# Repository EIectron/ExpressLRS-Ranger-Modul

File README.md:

<div align="center">
  <b>
   <h1>
      ExpressLRS Ranger
   </h1>
   <h6>
     V1
   </h6>
  </b>

</div>

## Features:
* E28 LoRa Modul
* ESP32 D4 Modul
* W2812B RGB Led
* I2C Screen Support

[Video](https://youtube.com/shorts/PznK_D05IgE)

### Build

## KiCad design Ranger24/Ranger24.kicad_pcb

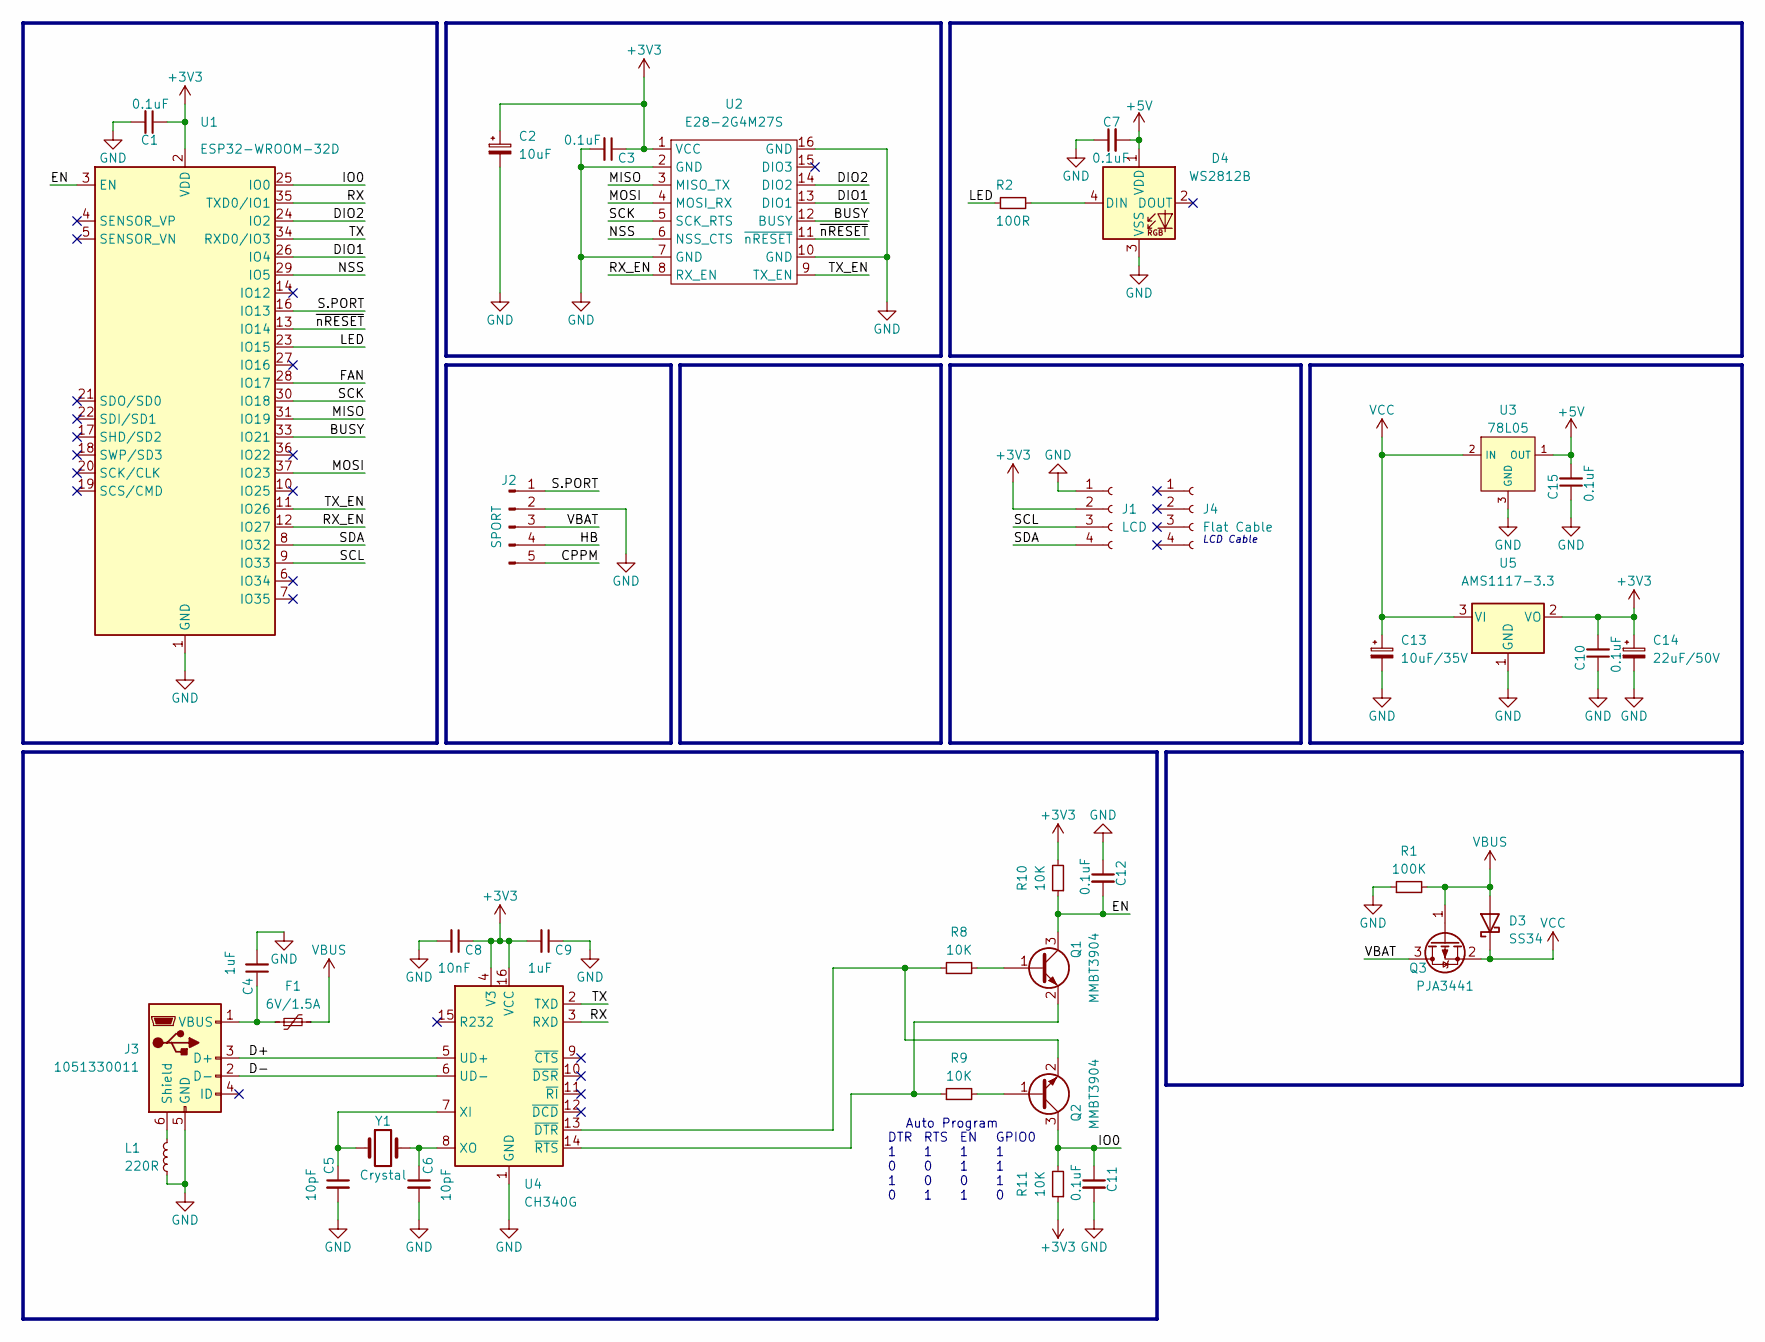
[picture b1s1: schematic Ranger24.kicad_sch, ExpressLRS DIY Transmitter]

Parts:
C1, C3, C7, C10, C11, C12, C15: 0.1uF; C_0603_1608Metric
C2: 10uF; CP_Elec_4x5.4
C4, C9: 1uF; C_0603_1608Metric
C5, C6: 10pF; C_0603_1608Metric
C8: 10nF; C_0603_1608Metric
C13: 10uF/35V; CP_Elec_5x5.3
C14: 22uF/50V; CP_Elec_6.3x5.7
D3: SS34; D_SMA
D4: WS2812B; LED_WS2812B_PLCC4_5.0x5.0mm_P3.2mm
F1: 6V/1.5A; Fuse_0805_2012Metric
J1: LCD; DS1020-05-04BT1
J2: SPORT; DS1023-10-1X5B81XTX
J3: 1051330011; USB_Micro-B_Molex-105133-0031
J4: Flat Cable
L1: 220R; L_0603_1608Metric
Q1, Q2: MMBT3904; SOT-23
Q3: PJA3441; SOT-23
R1: 100K; R_0603_1608Metric
R2: 100R; R_0603_1608Metric
R8, R9, R10, R11: 10K; R_0603_1608Metric
U1: ESP32-WROOM-32D; ESP32-WROOM-32
U2: E28-2G4M27S
U3: 78L05; SOT-23
U4: CH340G; SOIC-16_3.9x9.9mm_P1.27mm
U5: AMS1117-3.3; SOT-223-3_TabPin2
Y1: Crystal; Crystal_SMD_HC49-SD

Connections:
+3V3: C1.1, C2.1, C3.1, C8.1, C9.2, C10.2, C14.1, J1.2, R10.2, R11.1, U1.2 (VDD), U2.1 (VCC), U4.4 (V3), U4.16 (VCC), U5.2 (VO)
+5V: C7.2, C15.2, D4.1 (VDD), U3.1 (OUT)
/BUSY: U1.33 (IO21), U2.12 (BUSY)
/CPPM: J2.5
/D+: J3.3 (D+), U4.5 (UD+)
/D-: J3.2 (D-), U4.6 (UD-)
/DIO1: U1.26 (IO4), U2.13 (DIO1)
/DIO2: U1.24 (IO2), U2.14 (DIO2)
/EN: C12.2, Q1.3 (C), R10.1, U1.3 (EN)
/FAN: U1.28 (IO17)
/HB: J2.4
/IO0: C11.1, Q2.3 (C), R11.2, U1.25 (IO0)
/LED: R2.1, U1.23 (IO15)
/MISO: U1.31 (IO19), U2.3 (MISO_TX)
/MOSI: U1.37 (IO23), U2.4 (MOSI_RX)
/NSS: U1.29 (IO5), U2.6 (NSS_CTS)
/RX: U1.35 (TXD0/IO1), U4.3 (RXD)
/RX_EN: U1.12 (IO27), U2.8 (RX_EN)
/S.PORT: J2.1, U1.16 (IO13)
/SCK: U1.30 (IO18), U2.5 (SCK_RTS)
/SCL: J1.3, U1.9 (IO33)
/SDA: J1.4, U1.8 (IO32)
/TX: U1.34 (RXD0/IO3), U4.2 (TXD)
/TX_EN: U1.11 (IO26), U2.9 (TX_EN)
/VBAT: J2.3, Q3.3 (D)
/~nRESET: U1.13 (IO14), U2.11 (~nRESET)
GND: C1.2, C2.2, C3.2, C4.2, C5.2, C6.2, C7.1, C8.2, C9.1, C10.1, C11.2, C12.1, C13.2, C14.2, C15.1, D4.3 (VSS), J1.1, J2.2, J3.5 (GND), L1.1, R1.1, U1.1 (GND), U1.15 (GND), U1.38 (GND), U1.39 (GND), U2.2 (GND), U2.7 (GND), U2.10 (GND), U2.16 (GND), U3.3 (GND), U4.1 (GND), U5.1 (GND)
unnamed: D4.4 (DIN), R2.2
unnamed: J3.6 (Shield), L1.2
unnamed: C4.1, F1.1, J3.1 (VBUS)
unnamed: Q1.1 (B), R8.2
unnamed: Q1.2 (E), R9.1, U4.14 (~RTS)
unnamed: Q2.1 (B), R9.2
unnamed: Q2.2 (E), R8.1, U4.13 (~DTR)
unnamed: C5.1, U4.7 (XI), Y1.1
unnamed: C6.1, U4.8 (XO), Y1.2
VBUS: D3.2 (A), F1.2, Q3.1 (G), R1.2
VCC: C13.1, D3.1 (K), Q3.2 (S), U3.2 (IN), U5.3 (VI)

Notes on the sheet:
EN 1 1 0 1
DTR 1 0 1 0
Auto Program
GPIO0 1 1 1 0
RTS 1 0 0 1
LCD Cable

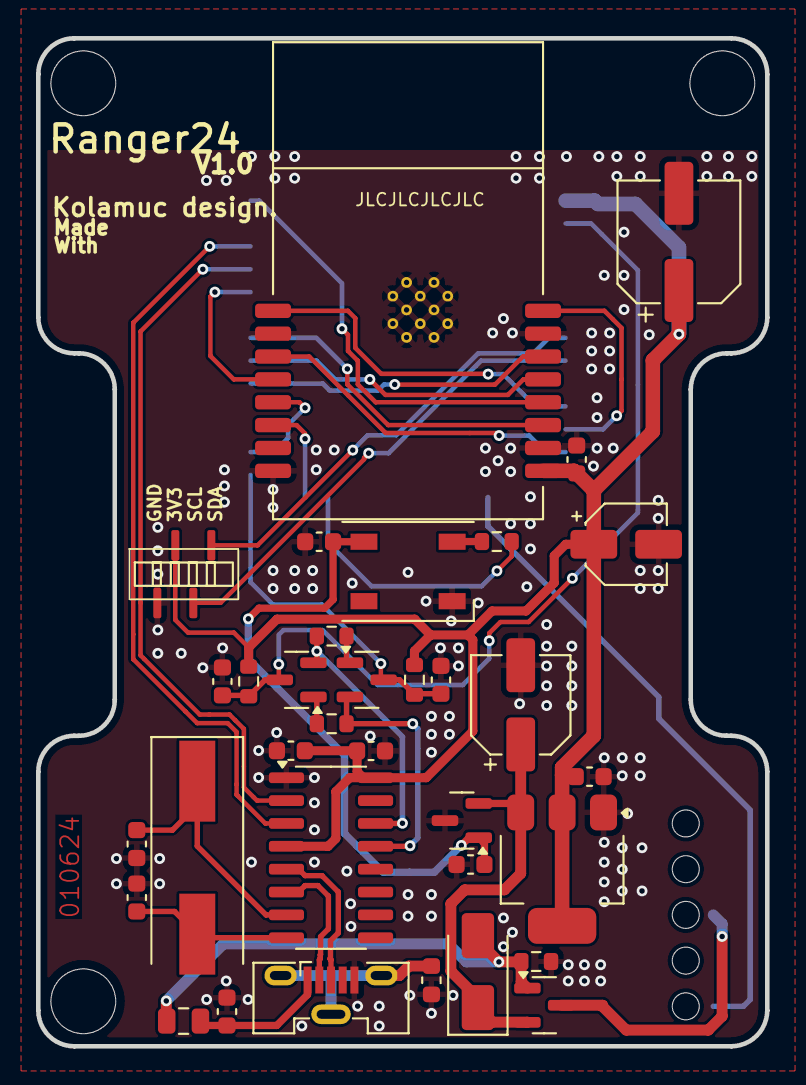
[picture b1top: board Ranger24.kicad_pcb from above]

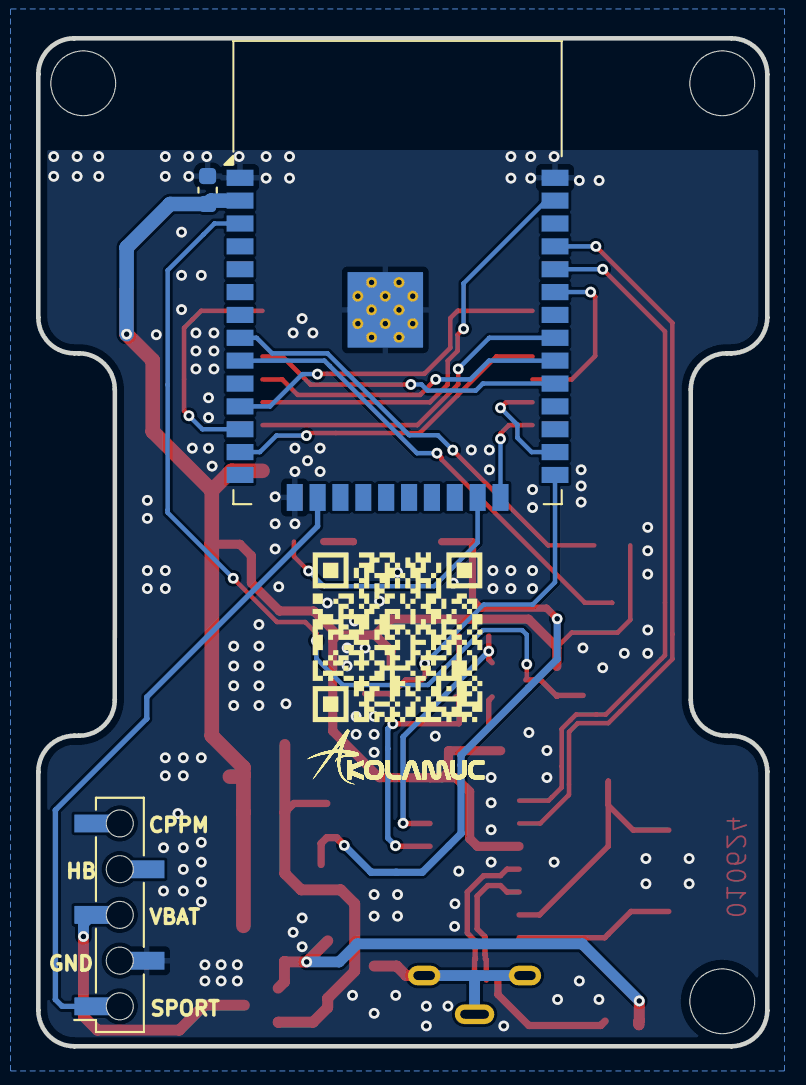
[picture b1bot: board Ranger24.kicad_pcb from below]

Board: 2 copper layers, 40.5 x 56.0 mm, 37 parts (3 on the bottom side), 35 nets.

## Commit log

2024-07-01 hw design done
2024-10-08 update
    edit screw holes
2024-10-16 update
    image and readme
2025-02-11 add some pics
2025-02-11 Update README.md
    add video url
